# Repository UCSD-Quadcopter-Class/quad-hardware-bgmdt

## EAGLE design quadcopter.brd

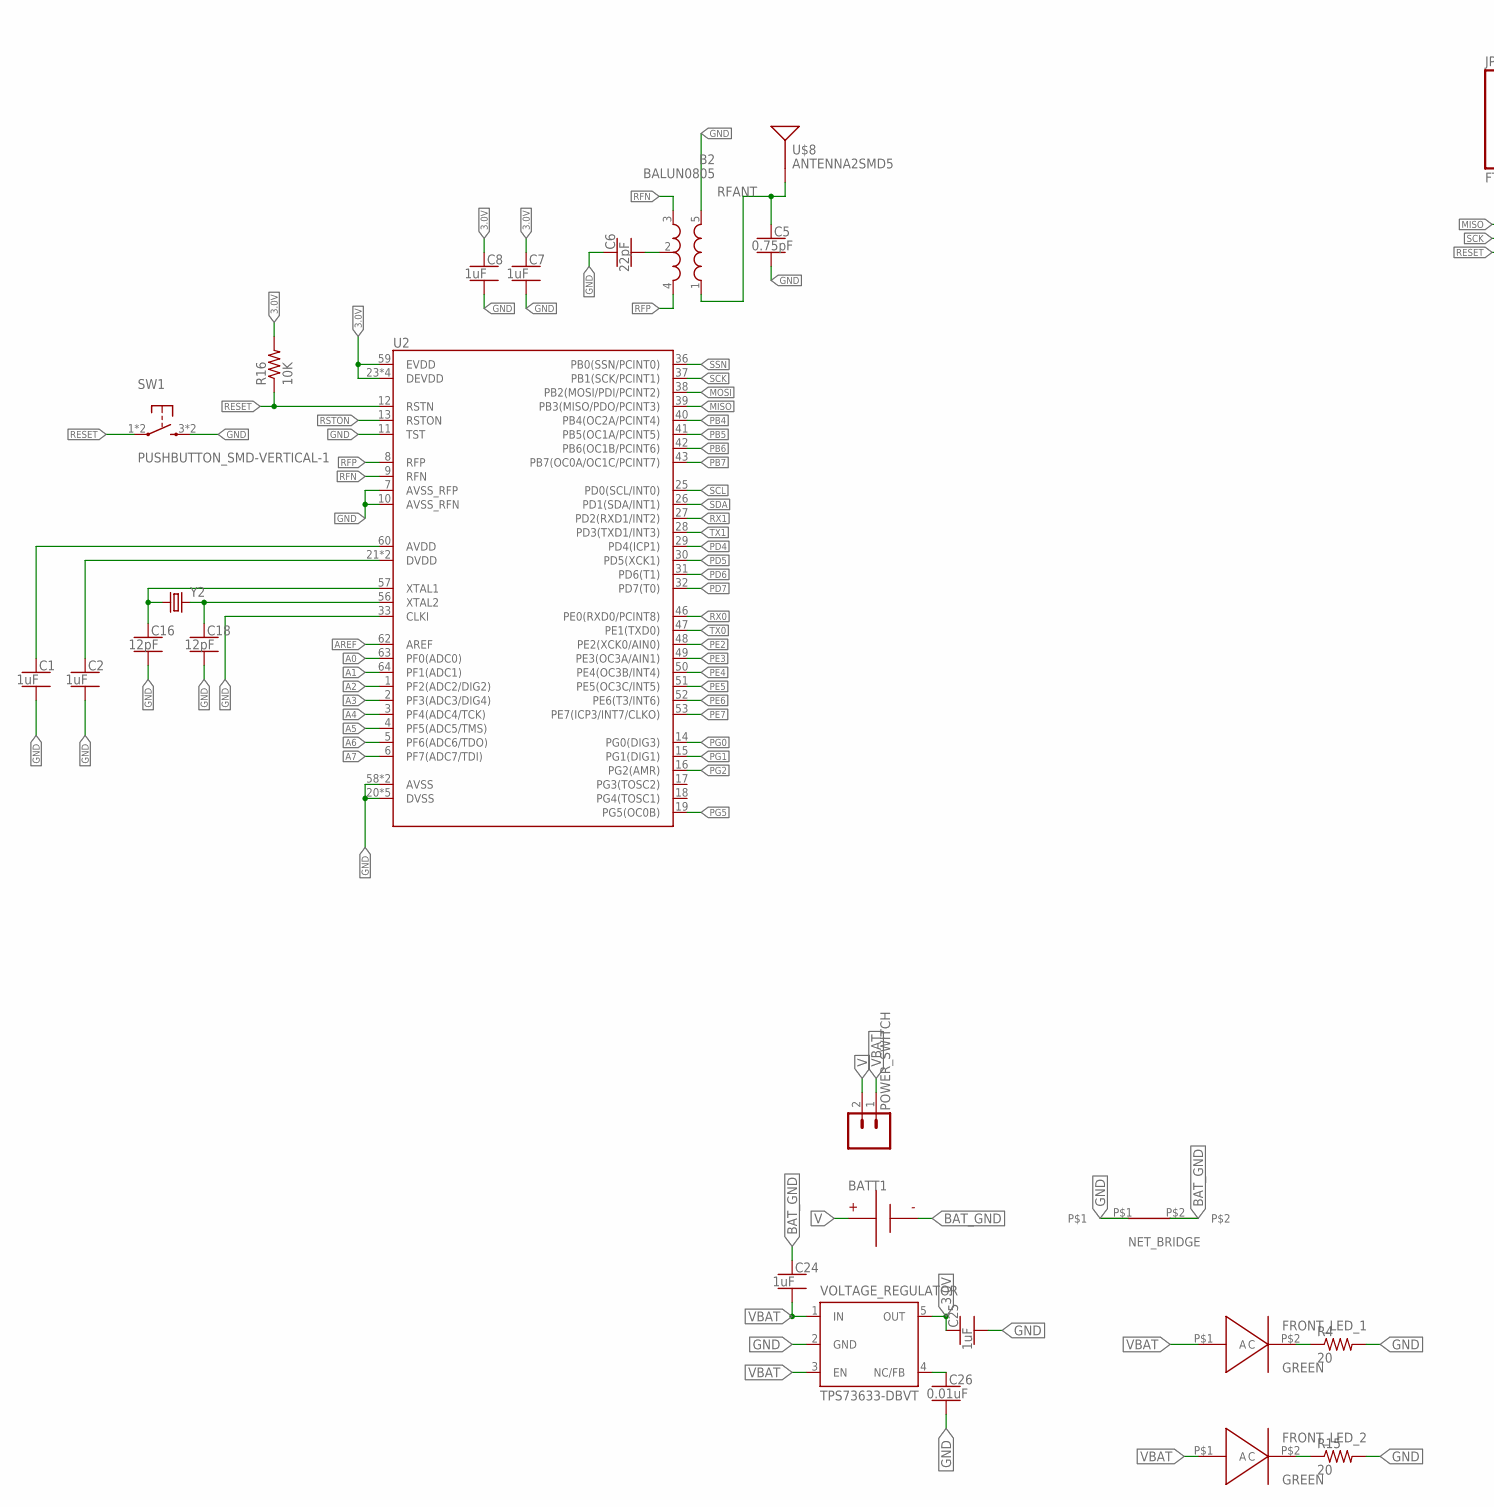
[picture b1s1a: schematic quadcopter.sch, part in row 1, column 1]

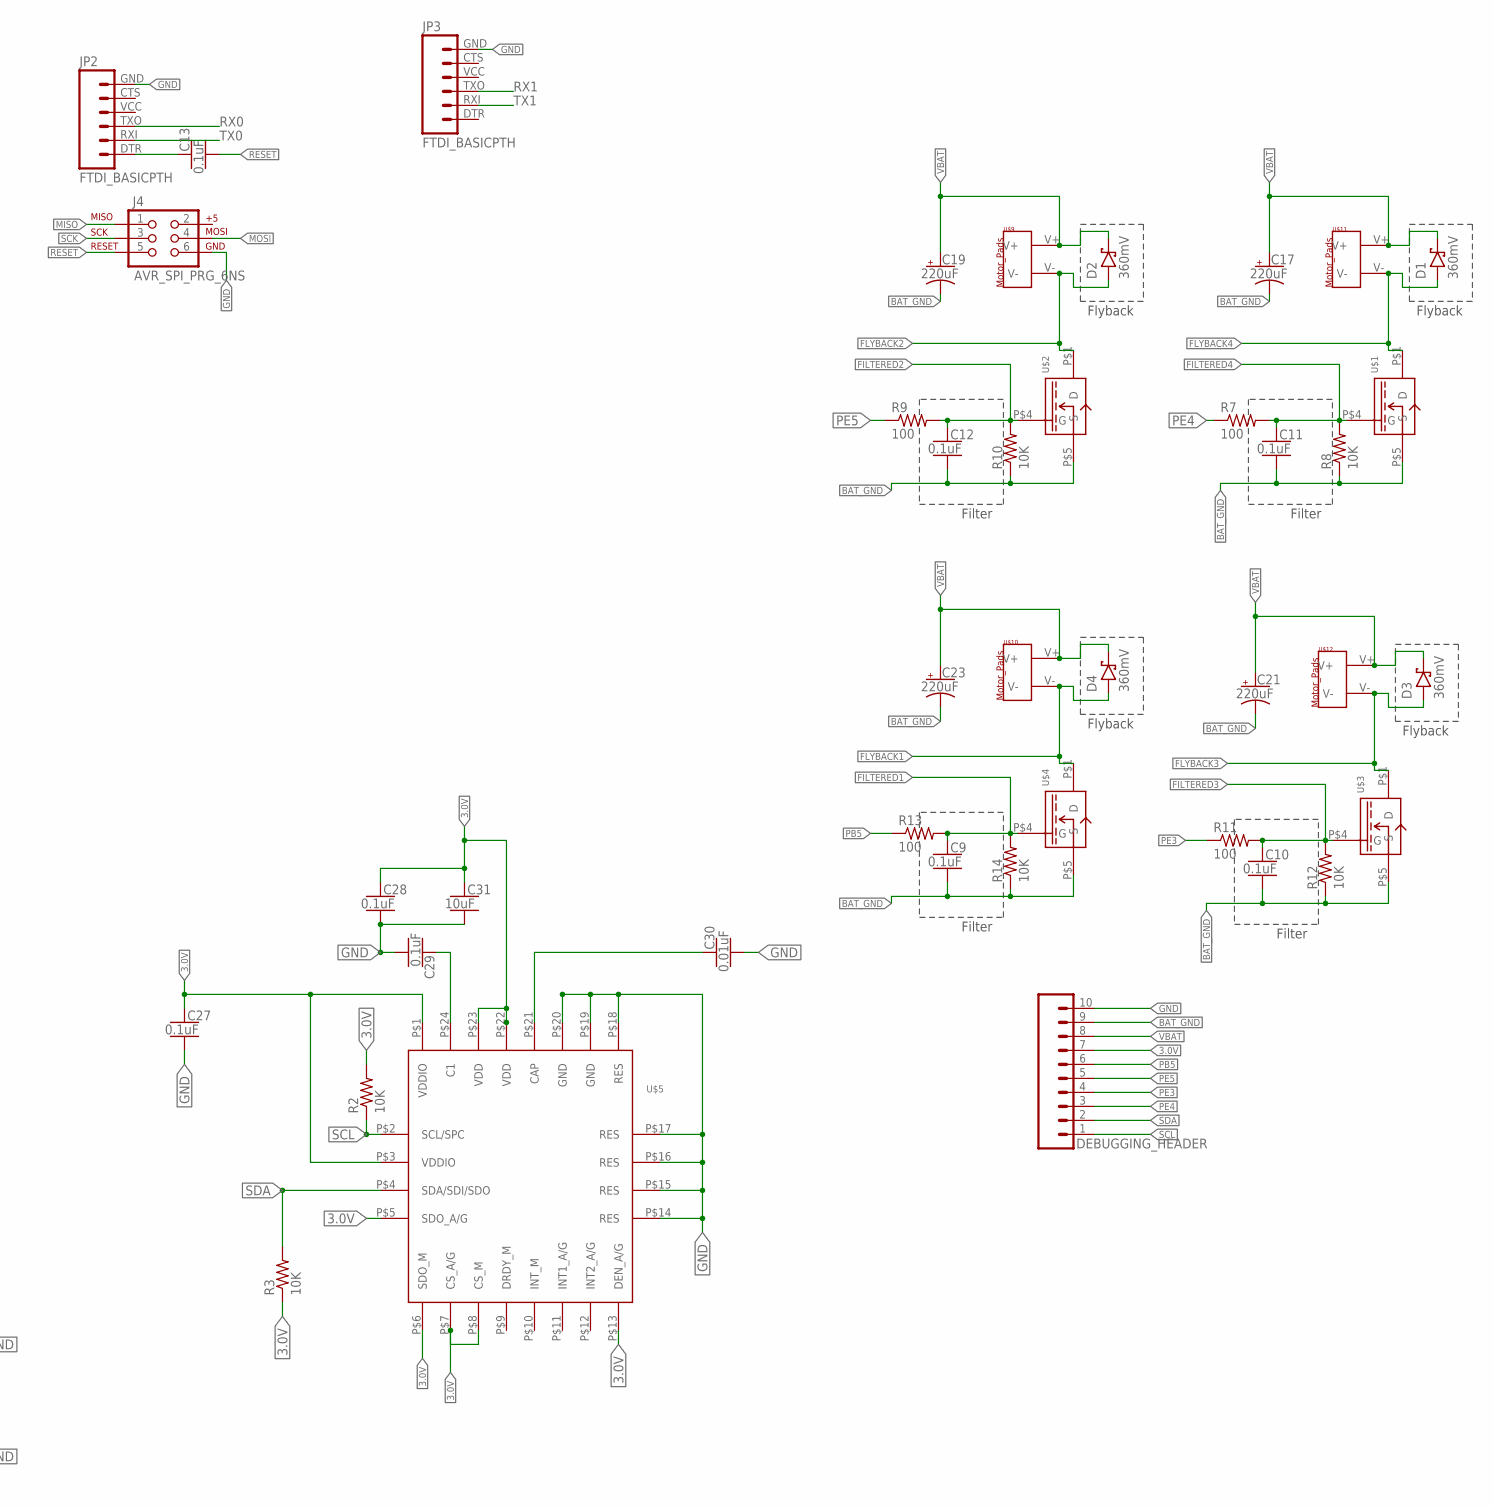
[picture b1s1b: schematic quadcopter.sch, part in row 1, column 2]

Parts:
B2: BALUN0805; BALUN
BATT1: BATTERY-HUBSAN-W/HOLDER; BATTERY-W/HOLDER-380MAH-HUBSAN
C1, C2, C7, C8, C24, C25: 1uF; CAPC2012X140_HS
C5: 0.75pF; CAPC2012X140_HS
C6: 22pF; CAPC2012X140_HS
C9, C10, C11, C12, C13, C27, C28, C29: 0.1uF; CAPC2012X140_HS
C16, C18: 12pF; CAPC2012X140_HS
C17, C19, C21, C23: 220uF; CAPMP7343X310_HS
C26, C30: 0.01uF; CAPC2012X140_HS
C31: 10uF; CAPC2012X140_HS
D1, D2, D3, D4: 360mV; SOD3716X135_HS
DEBUGGING_HEADER: SIP-10_TH-254X10-1; HDRV10W63P254_10X1_2540X254H838_HS
FRONT_LED_1, FRONT_LED_2: GREEN; KINGBRIGHT_LED
J4: AVR_SPI_PRG_6NS; 2X3-NS
JP2, JP3: FTDI_BASICPTH; FTDI_BASIC
NET_BRIDGE: NET_BRIDGE
POWER_SWITCH: MALE_HEADER_2POS-2X1-0.1IN; MALE_HEADER_2X1_0.1IN
R2, R3, R8, R10, R12, R14, R16: 10K; RESC2012X60_HS
R4, R15: 20; RESC2012X60_HS
R7, R9, R11, R13: 100; RESC2012X60_HS
SW1: PUSHBUTTON_SMD-VERTICAL-1; TE_FSM8JSMA_HS
U2: ATMEGA128RFA1; QFN-64
U$1, U$2, U$3, U$4: MOFSET_SI2302CDS-T1-E3CT-ND
U$5: IMU_497-14946-1-ND
U$8: ANTENNA2SMD5; ANTENNA-CHIP5
U$9, U$10, U$11, U$12: MOTOR_PADS
VOLTAGE_REGULATOR: TPS73633-DBVT; SOT23-DBV
Y2: CRYSTAL5X3; CRYSTAL-SMD-5X3

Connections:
3.0V: C7.1, C8.1, C25.1, C27.1, C28.1, C31.1, DEBUGGING_HEADER.7, R2.2, R3.1, R16.2, U2.23 (DEVDD), U2.34 (DEVDD), U2.44 (DEVDD), U2.54 (DEVDD), U2.59 (EVDD), U$5.P$1 (VDDIO), U$5.P$3 (VDDIO), U$5.P$5 (SDO_A/G), U$5.P$6 (SDO_M), U$5.P$7 (CS_A/G), U$5.P$8 (CS_M), U$5.P$13 (DEN_A/G), U$5.P$22 (VDD), U$5.P$23 (VDD), VOLTAGE_REGULATOR.5 (OUT)
A0: U2.63 (PF0(ADC0))
A1: U2.64 (PF1(ADC1))
A2: U2.1 (PF2(ADC2/DIG2))
A3: U2.2 (PF3(ADC3/DIG4))
A4: U2.3 (PF4(ADC4/TCK))
A5: U2.4 (PF5(ADC5/TMS))
A6: U2.5 (PF6(ADC6/TDO))
A7: U2.6 (PF7(ADC7/TDI))
AREF: U2.62 (AREF)
AVDD: C1.1, U2.60 (AVDD)
BAT_GND: BATT1.- (N), C9.2, C10.2, C11.2, C12.2, C17.2 (-), C19.2 (-), C21.2 (-), C23.2 (-), C24.1, DEBUGGING_HEADER.9, NET_BRIDGE.P$2, R8.1, R10.1, R12.1, R14.1, U$1.P$5 (S), U$2.P$5 (S), U$3.P$5 (S), U$4.P$5 (S)
DTR: C13.1, JP2.DTR (1)
DVDD: C2.1, U2.21 (DVDD), U2.22 (DVDD)
FILTERED1: C9.1, R13.2, R14.2, U$4.P$4 (G)
FILTERED2: C12.1, R9.2, R10.2, U$2.P$4 (G)
FILTERED3: C10.1, R11.2, R12.2, U$3.P$4 (G)
FILTERED4: C11.1, R7.2, R8.2, U$1.P$4 (G)
FLYBACK1: D4.A, U$4.P$1 (D), U$10.V-
FLYBACK2: D2.A, U$2.P$1 (D), U$9.V-
FLYBACK3: D3.A, U$3.P$1 (D), U$12.V-
FLYBACK4: D1.A, U$1.P$1 (D), U$11.V-
GND: B2.5 (GND), C1.2, C2.2, C5.2, C6.1, C7.2, C8.2, C16.2, C18.2, C25.2, C26.2, C27.2, C28.2, C29.2, C30.2, C31.2, DEBUGGING_HEADER.10, J4.6, JP2.GND (6), JP3.GND (6), NET_BRIDGE.P$1, R4.2, R15.2, SW1.3 (2), SW1.4 (2), U2.7 (AVSS_RFP), U2.10 (AVSS_RFN), U2.11 (TST), U2.20 (DVSS), U2.24 (DVSS), U2.33 (CLKI), U2.35 (DVSS), U2.45 (DVSS), U2.55 (DVSS), U2.58 (AVSS), U2.61 (AVSS), U$5.P$14 (RES), U$5.P$15 (RES), U$5.P$16 (RES), U$5.P$17 (RES), U$5.P$18 (RES), U$5.P$19 (GND), U$5.P$20 (GND), VOLTAGE_REGULATOR.2 (GND)
MISO: J4.1, U2.39 (PB3(MISO/PDO/PCINT3))
MOSI: J4.4, U2.38 (PB2(MOSI/PDI/PCINT2))
unnamed: FRONT_LED_1.P$2 (C), R4.1
unnamed: C30.1, U$5.P$21 (CAP)
unnamed: FRONT_LED_2.P$2 (C), R15.1
unnamed: B2.2 (GND), C6.2
unnamed: C29.1, U$5.P$24 (C1)
unnamed: C16.1, U2.57 (XTAL1), Y2.1
unnamed: C18.1, U2.56 (XTAL2), Y2.3 (2)
unnamed: C26.1, VOLTAGE_REGULATOR.4 (NC/FB)
PB4: U2.40 (PB4(OC2A/PCINT4))
PB5: DEBUGGING_HEADER.6, R13.1, U2.41 (PB5(OC1A/PCINT5))
PB6: U2.42 (PB6(OC1B/PCINT6))
PB7: U2.43 (PB7(OC0A/OC1C/PCINT7))
PD4: U2.29 (PD4(ICP1))
PD5: U2.30 (PD5(XCK1))
PD6: U2.31 (PD6(T1))
PD7: U2.32 (PD7(T0))
PE2: U2.48 (PE2(XCK0/AIN0))
PE3: DEBUGGING_HEADER.4, R11.1, U2.49 (PE3(OC3A/AIN1))
PE4: DEBUGGING_HEADER.3, R7.1, U2.50 (PE4(OC3B/INT4))
PE5: DEBUGGING_HEADER.5, R9.1, U2.51 (PE5(OC3C/INT5))
PE6: U2.52 (PE6(T3/INT6))
PE7: U2.53 (PE7(ICP3/INT7/CLKO))
PG0: U2.14 (PG0(DIG3))
PG1: U2.15 (PG1(DIG1))
PG2: U2.16 (PG2(AMR))
PG5: U2.19 (PG5(OC0B))
RESET: C13.2, J4.5, R16.1, SW1.1, SW1.2 (1), U2.12 (RSTN)
RFANT: B2.1 (IN), C5.1, U$8.FEED
RFN: B2.3 (OUT2), U2.9 (RFN)
RFP: B2.4 (OUT1), U2.8 (RFP)
RSTON: U2.13 (RSTON)
RX0: JP2.TXO (3), U2.46 (PE0(RXD0/PCINT8))
RX1: JP3.TXO (3), U2.27 (PD2(RXD1/INT2))
SCK: J4.3, U2.37 (PB1(SCK/PCINT1))
SCL: DEBUGGING_HEADER.1, R2.1, U2.25 (PD0(SCL/INT0)), U$5.P$2 (SCL/SPC)
SDA: DEBUGGING_HEADER.2, R3.2, U2.26 (PD1(SDA/INT1)), U$5.P$4 (SDA/SDI/SDO)
SSN: U2.36 (PB0(SSN/PCINT0))
TX0: JP2.RXI (2), U2.47 (PE1(TXD0))
TX1: JP3.RXI (2), U2.28 (PD3(TXD1/INT3))
V: BATT1.+, POWER_SWITCH.2
VBAT: C17.1 (+), C19.1 (+), C21.1 (+), C23.1 (+), C24.2, D1.C, D2.C, D3.C, D4.C, DEBUGGING_HEADER.8, FRONT_LED_1.P$1 (A), FRONT_LED_2.P$1 (A), POWER_SWITCH.1, U$9.V+, U$10.V+, U$11.V+, U$12.V+, VOLTAGE_REGULATOR.1 (IN), VOLTAGE_REGULATOR.3 (EN)

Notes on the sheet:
Filter
Flyback

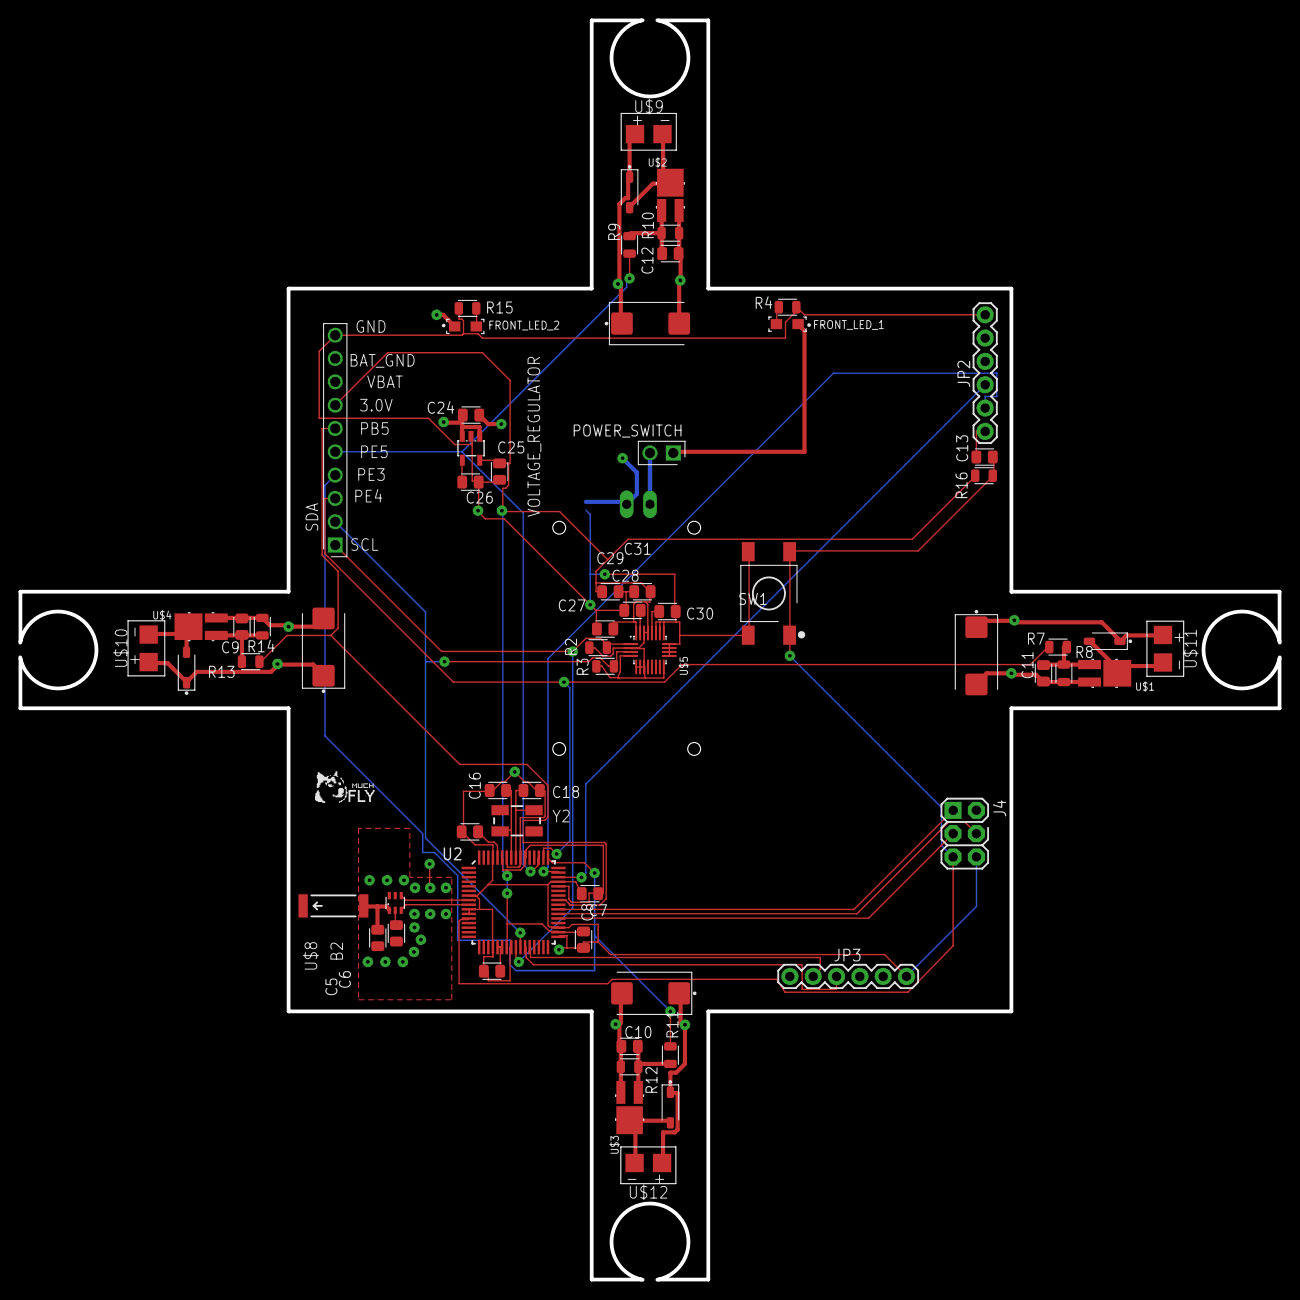
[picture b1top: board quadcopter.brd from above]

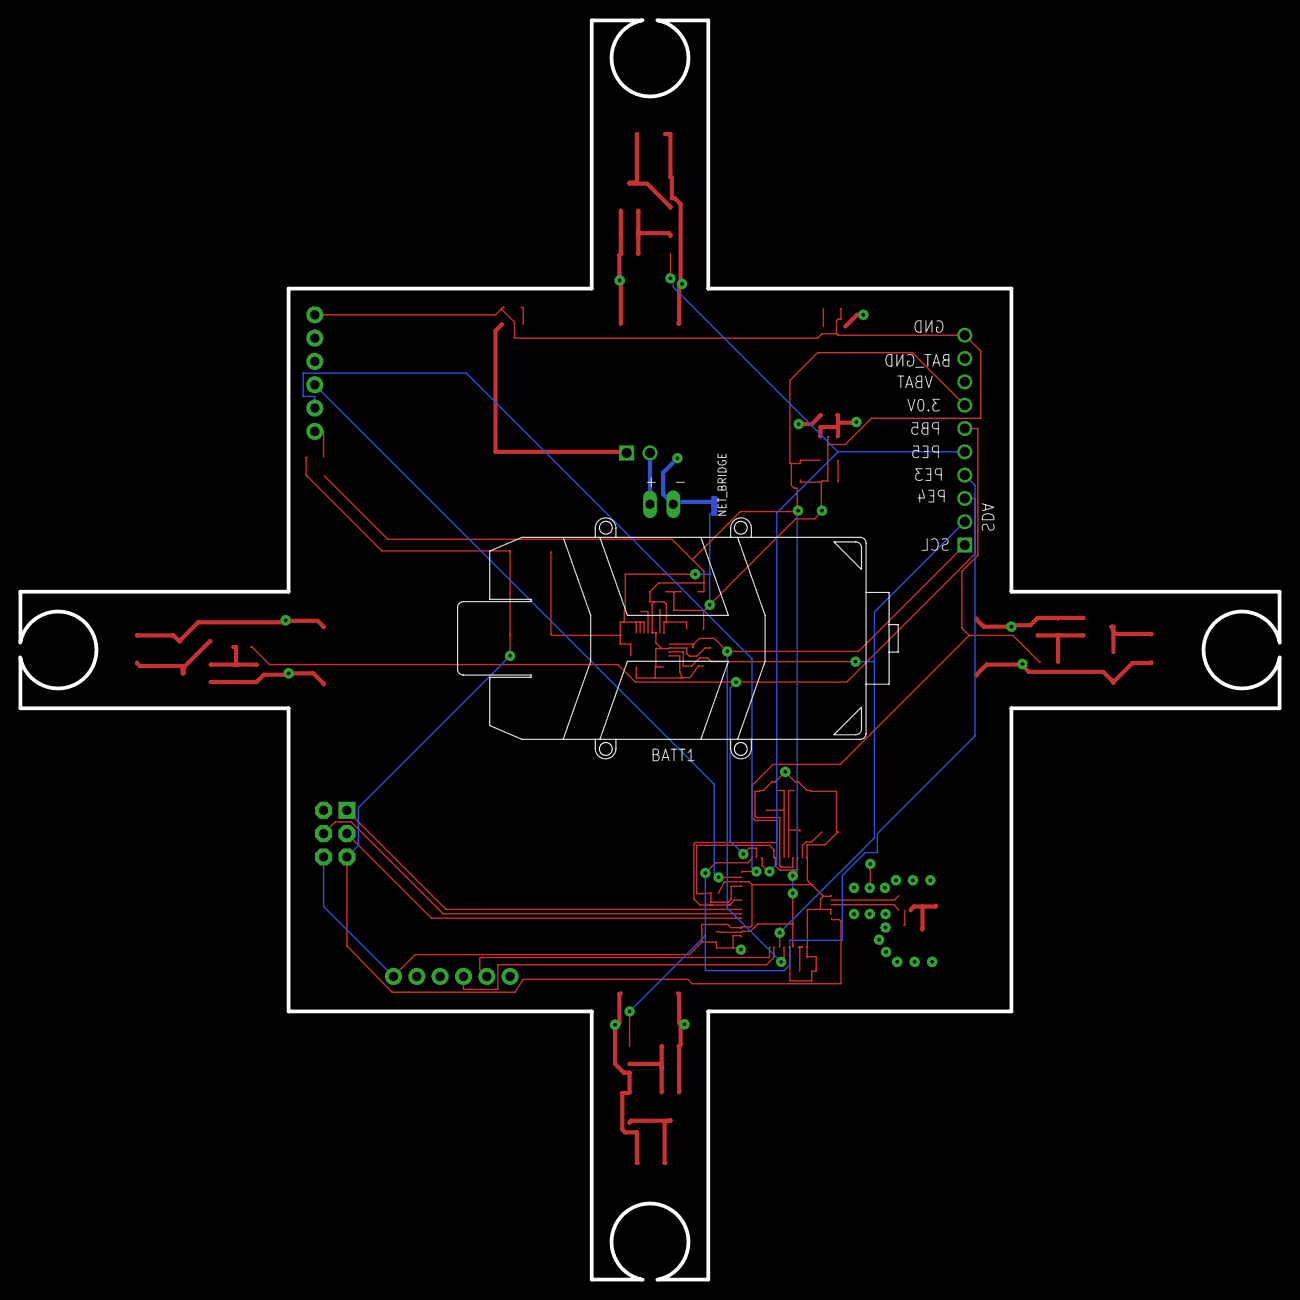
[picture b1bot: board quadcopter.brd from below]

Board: 4 copper layers, 137.2 x 137.2 mm, 67 parts (2 on the bottom side), 41 nets.

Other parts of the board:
U$7: DOGE

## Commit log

2016-04-07 import
2016-04-12 part library
2016-04-21 Removing StaringPoint.sh
2016-04-28 Package with motor geometry
2016-05-07 updates to make it pass sanity checks
2017-03-22 cleanup
2017-03-26 new folder
2017-04-10 Added motor driver schematic
2017-04-19 Add .gitignore
2017-04-19 Place microcontroller and motors
2017-04-19 voltage reg added
2017-04-19 Finish MC, Breakout, and Motors
2017-04-19 IMU finished, LED lib added but empty
2017-04-19 Added LEDs into schematic in series, no resistor necessary
2017-04-20 Added supporting docs for LEDs
2017-04-20 Everything seems to be in order
2017-04-20 Submission
2017-04-24 Lab4b I
2017-04-24 Lab4b design review
2017-04-25 Added pull up resistors, fixed leds
2017-04-26 Fix quadcopter shematic and parts in quadcopter_jay
2017-04-27 Added all parts to board but have yet to run autorouter/set up the traces
2017-04-27 instructior review of original schematic
2017-04-27 Fixed some schematic things, still need to fix swanson notes and the motor drivers
2017-05-01 Modify Motor Driver and check off components on swanson_design_review
2017-05-02 Finish Board Layers (still need to route
2017-05-03 Push Board
2017-05-03 Ran Autorouter but did not fix errros
2017-05-03 added motor holes
2017-05-04 Design Review -- Board
2017-05-04 Discuss Review
2017-05-11 Board is done
2017-05-11 Finish
2017-05-16 Finished Board (again)
2017-05-16 CompilingGerber
2017-05-16 Move Caps closer to microcontroller
2017-05-16 Almost Completely Done
2017-05-16 Finalize Board (Add Reviewers)
2017-05-16 Forgot to approve stop mask errors
2017-05-16 more schematic comments from swanson
2017-05-19 Current Additions
2017-05-23 New Revision
2017-05-23 Board finally passes DFM
2017-05-23 Update board_review_swanson.txt
    Comment on diodes.
2017-05-23 Add Everything
2017-05-23 Passing DFM again
2017-05-23 Update CAM Files
2017-05-23 Whoops, deleted quadcopter schematic
